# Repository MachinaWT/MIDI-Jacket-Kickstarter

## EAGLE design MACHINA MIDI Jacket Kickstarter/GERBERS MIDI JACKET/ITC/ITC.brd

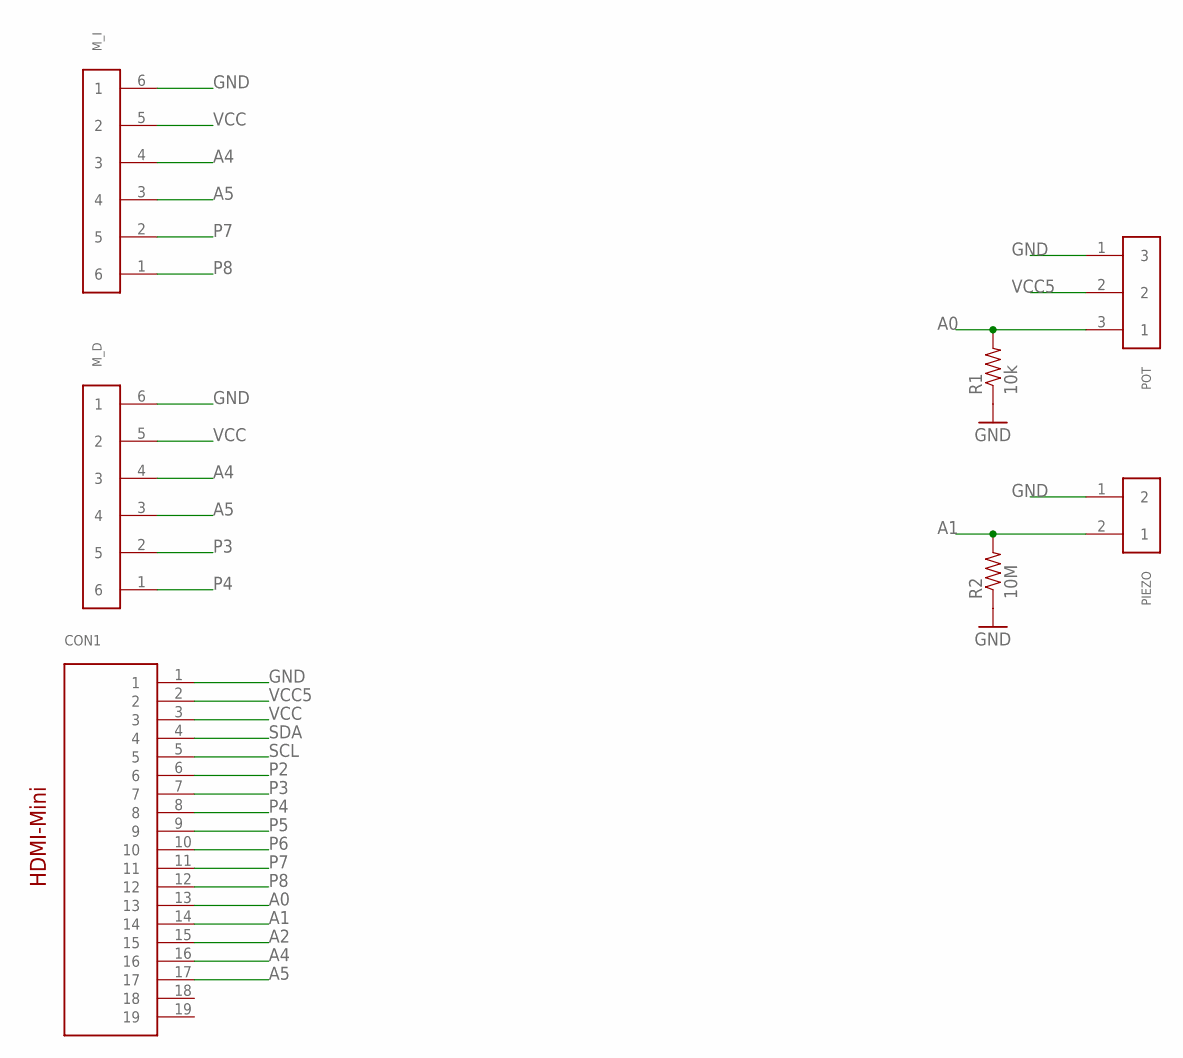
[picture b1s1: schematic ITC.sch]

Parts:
CON1: HDMIMINI
M_D: 653106131822
M_I: 653106131822
PIEZO: 653102131822
POT: 653103131822
R1: 10k; 0402-RES
R2: 10M; 0402-RES

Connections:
A0: CON1.13, POT.3 (1), R1.2
A1: CON1.14, PIEZO.2 (1), R2.2
A2: CON1.15
A4: CON1.16, M_D.4 (3), M_I.4 (3)
A5: CON1.17, M_D.3 (4), M_I.3 (4)
GND: CON1.1, M_D.6 (1), M_I.6 (1), PIEZO.1 (2), POT.1 (3), R1.1, R2.1
P2: CON1.6
P3: CON1.7, M_D.2 (5)
P4: CON1.8, M_D.1 (6)
P5: CON1.9
P6: CON1.10
P7: CON1.11, M_I.2 (5)
P8: CON1.12, M_I.1 (6)
SCL: CON1.5
SDA: CON1.4
VCC: CON1.3, M_D.5 (2), M_I.5 (2)
VCC5: CON1.2, POT.2

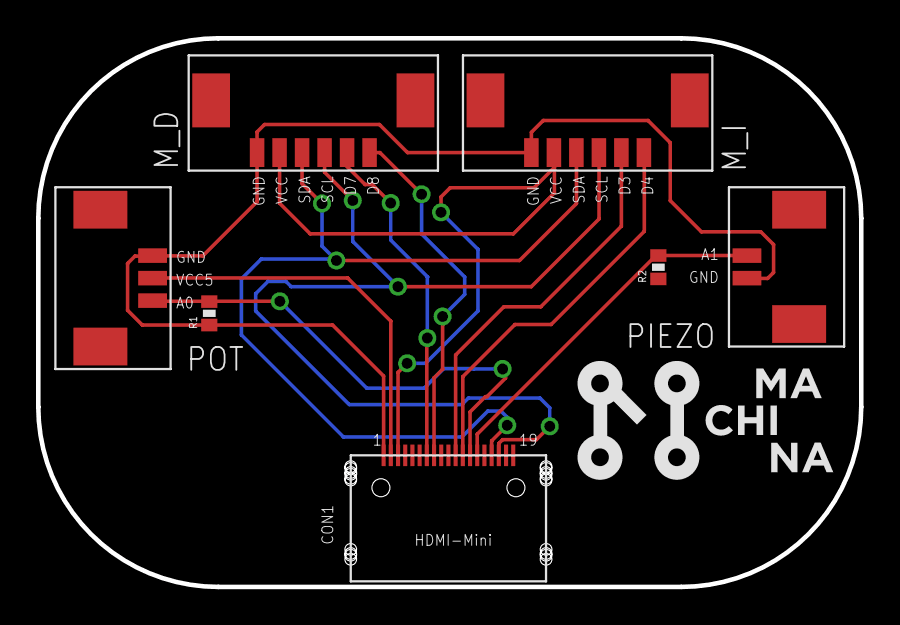
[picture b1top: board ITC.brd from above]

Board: 2 copper layers, 45.7 x 30.5 mm, 7 parts (0 on the bottom side), 11 nets.

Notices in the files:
parts and their libraries:
Wuerth_Elektronik_eiCan_09_Wire_to_Board: Copyright: Würth Elektronik
SparkFun-Passives: Licensing: CC v3.0 Share-Alike You are welcome to use this library for commercial purposes.
